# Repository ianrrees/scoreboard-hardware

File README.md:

# scoreboard-hardware
PCB design files for an I2C controlled LED 7-segment digit.

## TODO

  * Explain the idea behind the top panel
  * Make sure the through hole LED silkscreen is visible after parts are placed

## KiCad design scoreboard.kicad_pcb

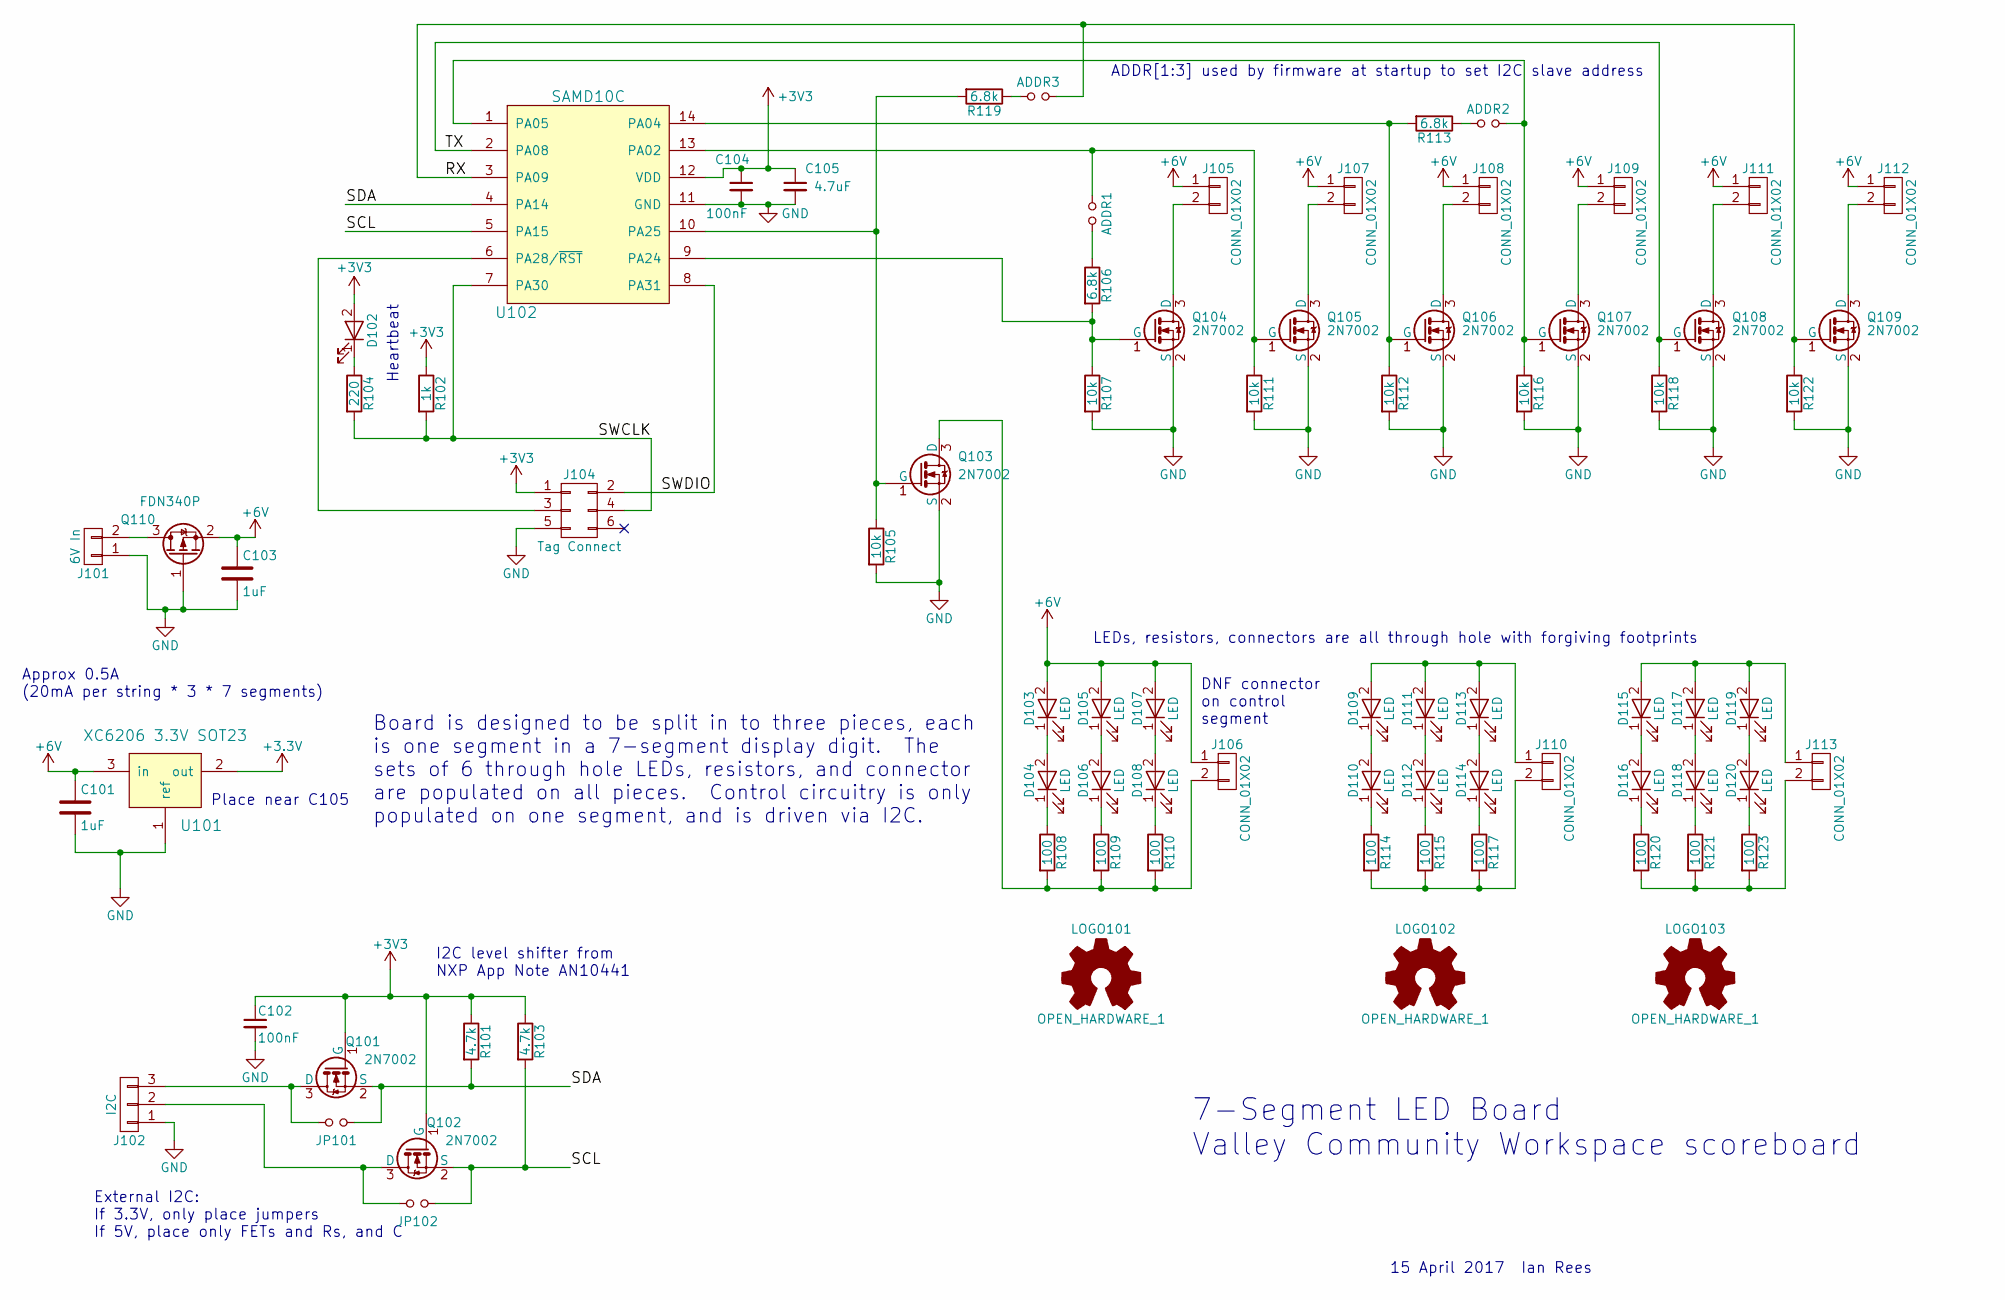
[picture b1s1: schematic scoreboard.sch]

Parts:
ADDR1, ADDR2, ADDR3: Jumper_NO_Small; solder_jumper
C101, C103: 1uF; C_0603_HandSoldering
C102, C104: 100nF; C_0603_HandSoldering
C105: 4.7uF; C_0603_HandSoldering
D102: LED; led_0603_HandSoldering
D103, D104, D105, D106, D107, D108, D109, D110, D111, D112, D113, D114, D115, D116, D117, D118, D119, D120: LED; LED_D5.0mm
J101: 6V In; AK300-min
J102: I2C; Molex_MicroLatch-53253-0370_03x2.00mm_Straight
J104: Tag Connect; Tag-Connect_TC2030-IDC-FP
J105, J106, J107, J108, J109, J110, J111, J112, J113: CONN_01X02; AK300-min
JP101, JP102: Jumper_NO_Small; R_0603_HandSoldering
LOGO101, LOGO102, LOGO103: OPEN_HARDWARE_1; Symbol_OSHW-Logo_CopperTop
Q101, Q102, Q103, Q104, Q105, Q106, Q107, Q108, Q109: 2N7002; SOT-23
Q110: FDN340P; SOT-23_Handsoldering
R101, R103: 4.7k; R_0603_HandSoldering
R102: 1k; R_0603_HandSoldering
R104: 220; R_0603_HandSoldering
R105, R107, R111, R112, R116, R118, R122: 10k; R_0603_HandSoldering
R106, R113, R119: 6.8k; R_0603_HandSoldering
R108, R109, R110, R114, R115, R117, R120, R121, R123: 100; R_Axial_DIN0411_L9.9mm_D3.6mm_P15.24mm_Horizontal
U101: XC6206 3.3V SOT23; SOT-23_Handsoldering
U102: SAMD10C; SOIC-14_3.9x8.7mm_Pitch1.27mm

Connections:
+6V: C101.1, C103.1, D103.2 (A), D105.2 (A), D107.2 (A), J105.1, J106.1, J107.1, J108.1, J109.1, J111.1, J112.1, Q110.2 (S), U101.3 (in)
/RX: ADDR3.2, Q109.1 (G), R122.1, U102.3 (PA09)
/SCL: JP102.2, Q102.2 (S), R103.2, U102.5 (PA15)
/SDA: JP101.2, Q101.2 (S), R101.2, U102.4 (PA14)
/SWCLK: J104.4, R102.2, R104.2, U102.7 (PA30)
/SWDIO: J104.2, U102.8 (PA31)
/TX: Q108.1 (G), R118.1, U102.2 (PA08)
GND: C101.2, C102.2, C103.2, C104.2, C105.2, J101.1, J102.1, J104.5, Q103.2 (S), Q104.2 (S), Q105.2 (S), Q106.2 (S), Q107.2 (S), Q108.2 (S), Q109.2 (S), Q110.1 (G), R105.2, R107.2, R111.2, R112.2, R116.2, R118.2, R122.2, U101.1 (ref), U102.11 (GND)
unnamed: ADDR1.1, Q105.1 (G), R111.1, U102.13 (PA02)
unnamed: ADDR1.2, R106.1
unnamed: ADDR2.1, R113.1
unnamed: ADDR2.2, Q107.1 (G), R116.1, U102.1 (PA05)
unnamed: ADDR3.1, R119.1
unnamed: D102.1 (K), R104.1
unnamed: D103.1 (K), D104.2 (A)
unnamed: D104.1 (K), R108.1
unnamed: D105.1 (K), D106.2 (A)
unnamed: D106.1 (K), R109.1
unnamed: D107.1 (K), D108.2 (A)
unnamed: D108.1 (K), R110.1
unnamed: D109.1 (K), D110.2 (A)
unnamed: D109.2 (A), D111.2 (A), D113.2 (A), J110.1
unnamed: D110.1 (K), R114.1
unnamed: D111.1 (K), D112.2 (A)
unnamed: D112.1 (K), R115.1
unnamed: D113.1 (K), D114.2 (A)
unnamed: D114.1 (K), R117.1
unnamed: D115.1 (K), D116.2 (A)
unnamed: D115.2 (A), D117.2 (A), D119.2 (A), J113.1
unnamed: D116.1 (K), R120.1
unnamed: D117.1 (K), D118.2 (A)
unnamed: D118.1 (K), R121.1
unnamed: D119.1 (K), D120.2 (A)
unnamed: D120.1 (K), R123.1
unnamed: J101.2, Q110.3 (D)
unnamed: J102.2, JP102.1, Q102.3 (D)
unnamed: J102.3, JP101.1, Q101.3 (D)
unnamed: J104.3, U102.6 (PA28/~RST)
unnamed: J105.2, Q104.3 (D)
unnamed: J106.2, Q103.3 (D), R108.2, R109.2, R110.2
unnamed: J107.2, Q105.3 (D)
unnamed: J108.2, Q106.3 (D)
unnamed: J109.2, Q107.3 (D)
unnamed: J110.2, R114.2, R115.2, R117.2
unnamed: J111.2, Q108.3 (D)
unnamed: J112.2, Q109.3 (D)
unnamed: J113.2, R120.2, R121.2, R123.2
unnamed: Q103.1 (G), R105.1, R119.2, U102.10 (PA25)
unnamed: Q104.1 (G), R106.2, R107.1, U102.9 (PA24)
unnamed: Q106.1 (G), R112.1, R113.2, U102.14 (PA04)

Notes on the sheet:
External I2C: If 3.3V, only place jumpers If 5V, place only FETs and Rs, and C
I2C level shifter from NXP App Note AN10441
Heartbeat
LEDs, resistors, connectors are all through hole with forgiving footprints
Board is designed to be split in to three pieces, each is one segment in a 7-segment display digit. The sets of 6 through hole LEDs, resistors, and connector are populated on all pieces. Control circuitry is only populated on one segment, and is driven via I2C.
DNF connector on control segment
ADDR[1:3] used by firmware at startup to set I2C slave address
7-Segment LED Board Valley Community Workspace scoreboard
15 April 2017 Ian Rees
Place near C105
Approx 0.5A (20mA per string * 3 * 7 segments)

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
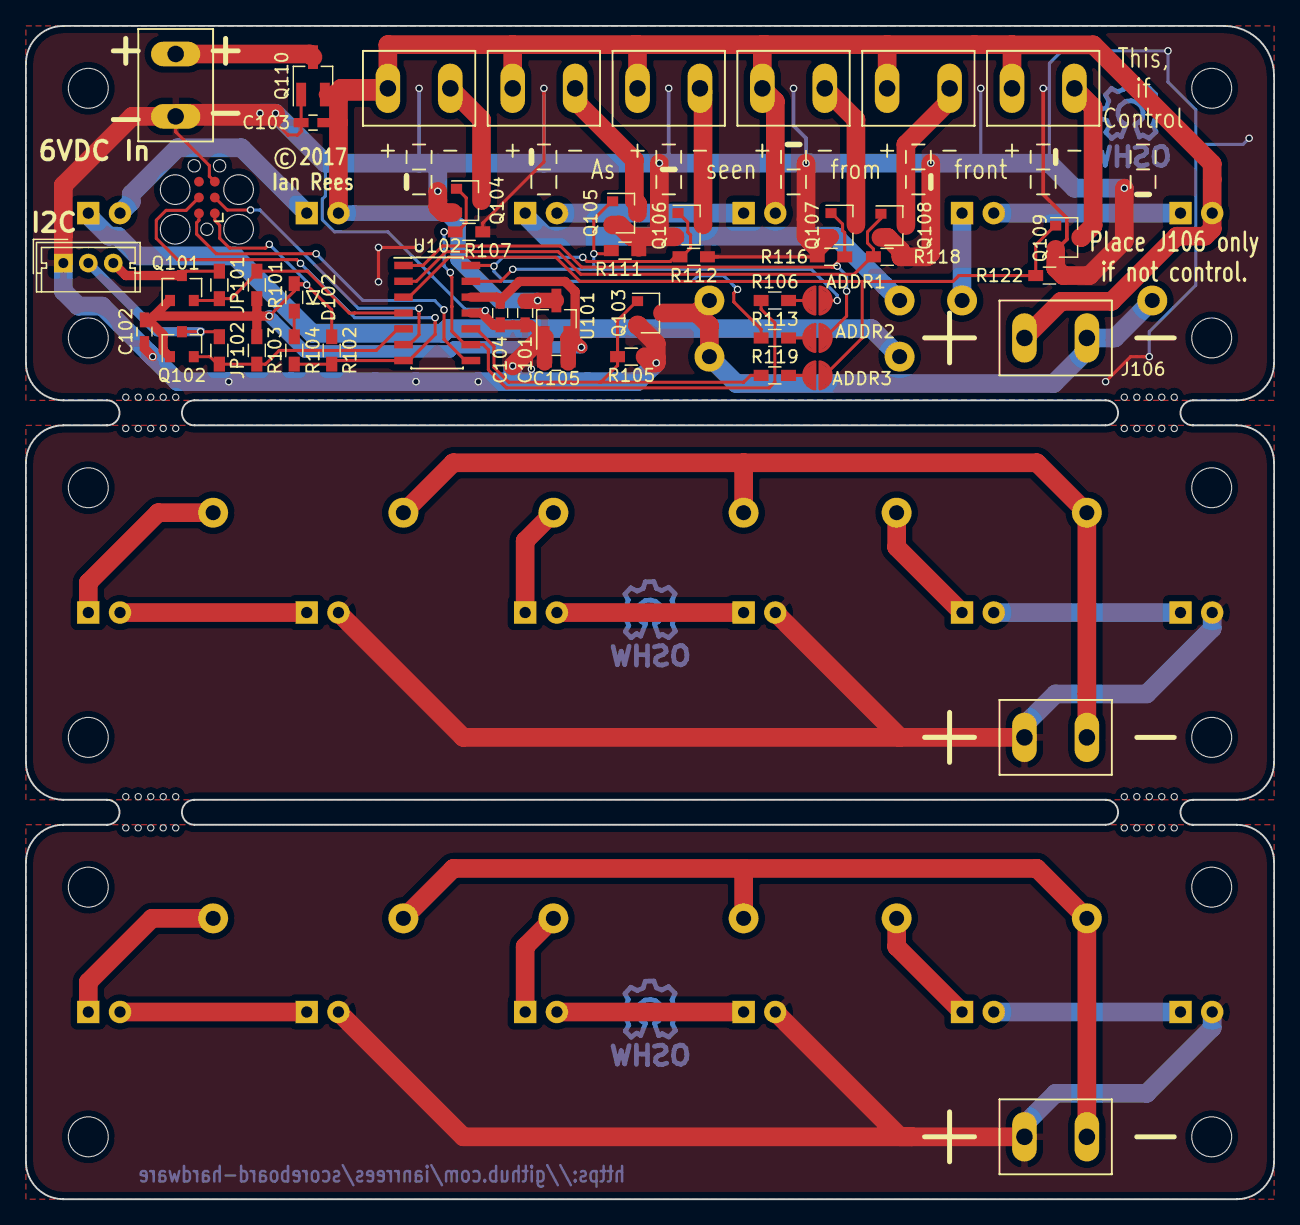
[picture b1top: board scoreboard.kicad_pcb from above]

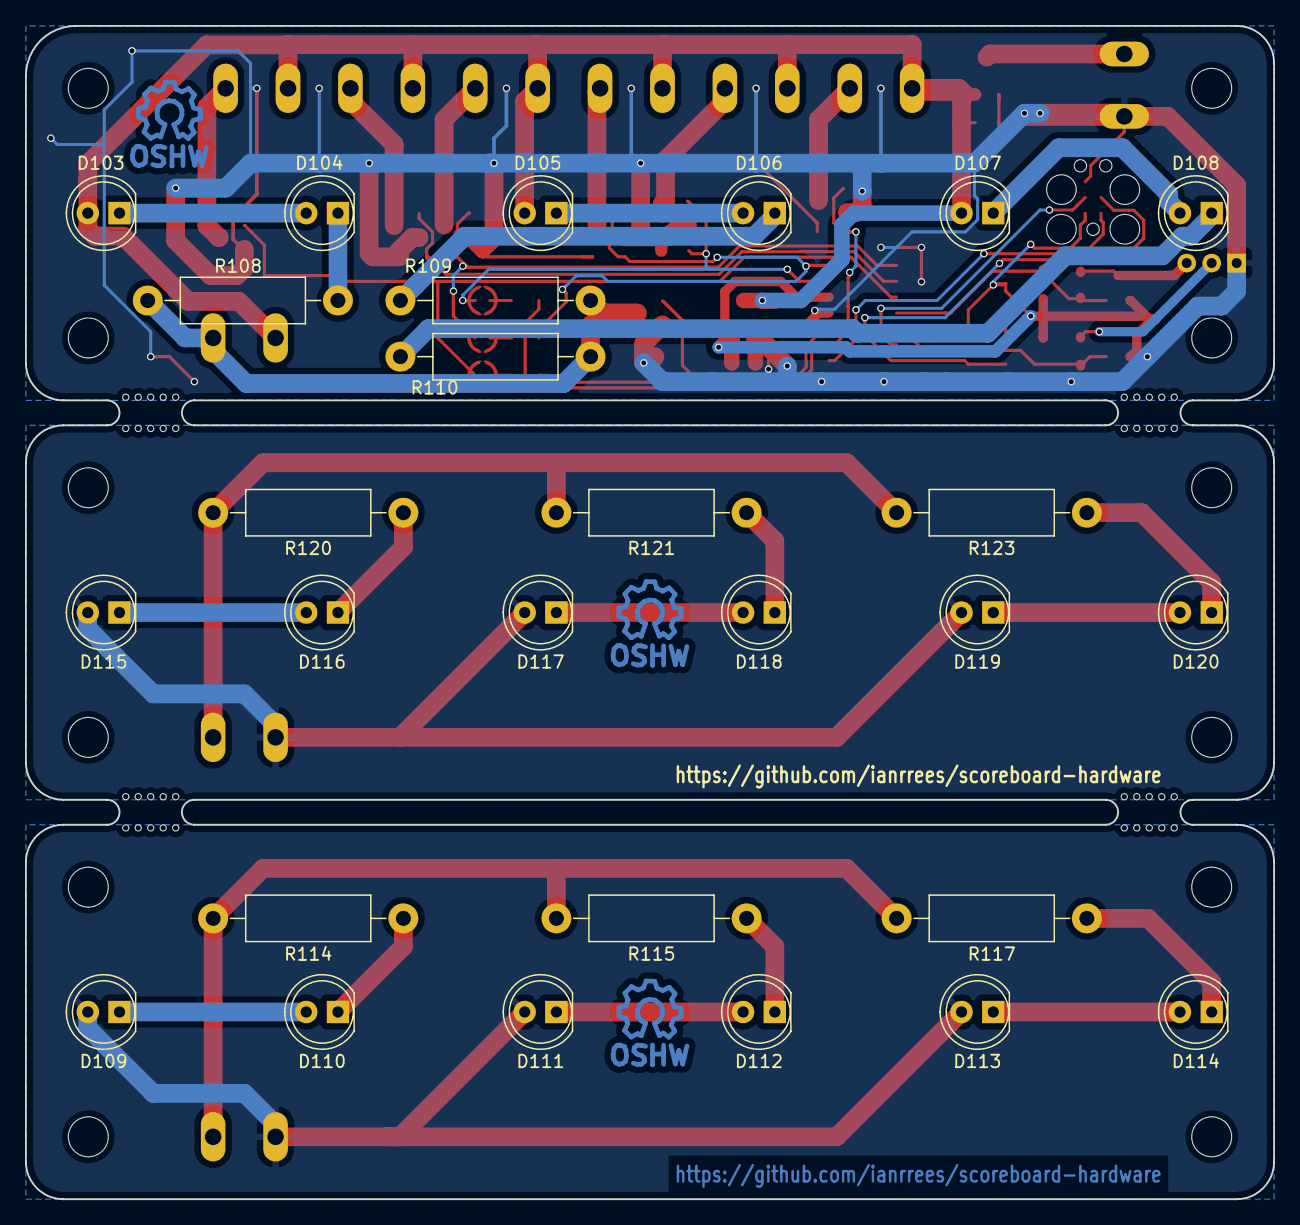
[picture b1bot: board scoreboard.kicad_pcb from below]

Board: 2 copper layers, 100.0 x 94.0 mm, 79 parts (30 on the bottom side), 51 nets.

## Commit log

2017-04-15 First cut at a schematic
2017-04-29 Prepare for first order
2017-05-03 PCB updated and gerbers added as ordered
